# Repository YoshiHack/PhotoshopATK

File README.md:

## Summary

PhotoshopATK is a compact, single-handed macropad designed to make editing in Adobe Photoshop faster and more efficient. It gives you quick access to your most-used editing commands so you can focus on creating instead of hunting for keyboard shortcuts. The macropad is lightweight, easy to use, and built for speed during creative work.

---
## Description 

PhotoshopATK streamlines Photoshop workflows by putting essential actions—such as undo, redo, and tool shortcuts—on dedicated physical buttons. This reduces repetitive keyboard movements, speeds up editing, and makes the overall process smoother and more comfortable.

---
## Case

The case is fully 3D-printed and built to fit within the Hackpad size requirements.
It includes:

Top shell

Bottom shell

Mounting space for the XIAO RP2040

Clearance for the PCB and switches

---
## PCB

The PCB is designed to support four mechanical switches connected directly to the XIAO RP2040. It remains compact and meets the 100×100 mm rule.

---
## Firmware

The firmware is written in KMK (CircuitPython) and maps the macropad buttons to Photoshop editing shortcuts.

Example actions:

Undo – Ctrl + Z

Redo (Photoshop) – Ctrl + Shift + Z

Other tools or shortcuts as needed

Firmware file:
/Firmware/main.py

---
## BOM (Bill Of Materiels) 

Item	Quantity	Notes
Seeed Studio XIAO RP2040	1	Main MCU
Mechanical Switches	4	Any MX-style switch
Custom PCB	1	Designed in KiCad
3D Printed Case	1 set	Top + Bottom
Keycaps	4	Any compatible keycaps
Wires/Solder	—	For assembly

---
## 📁 Repository Structure

/CAD
    PhotoshopATK.step

/PCB
    PhotoshopATK.kicad_pcb
    PhotoshopATK.kicad_sch
    PhotoshopATK.kicad_pro

/Firmware
    main.py

README.md

---
## Instructions 

Flash the KMK firmware to your XIAO RP2040

Place main.py inside the KMK folder

Connect the macropad to your computer

Open Photoshop and enjoy the faster workflow

Open-source project — feel free to build on it!

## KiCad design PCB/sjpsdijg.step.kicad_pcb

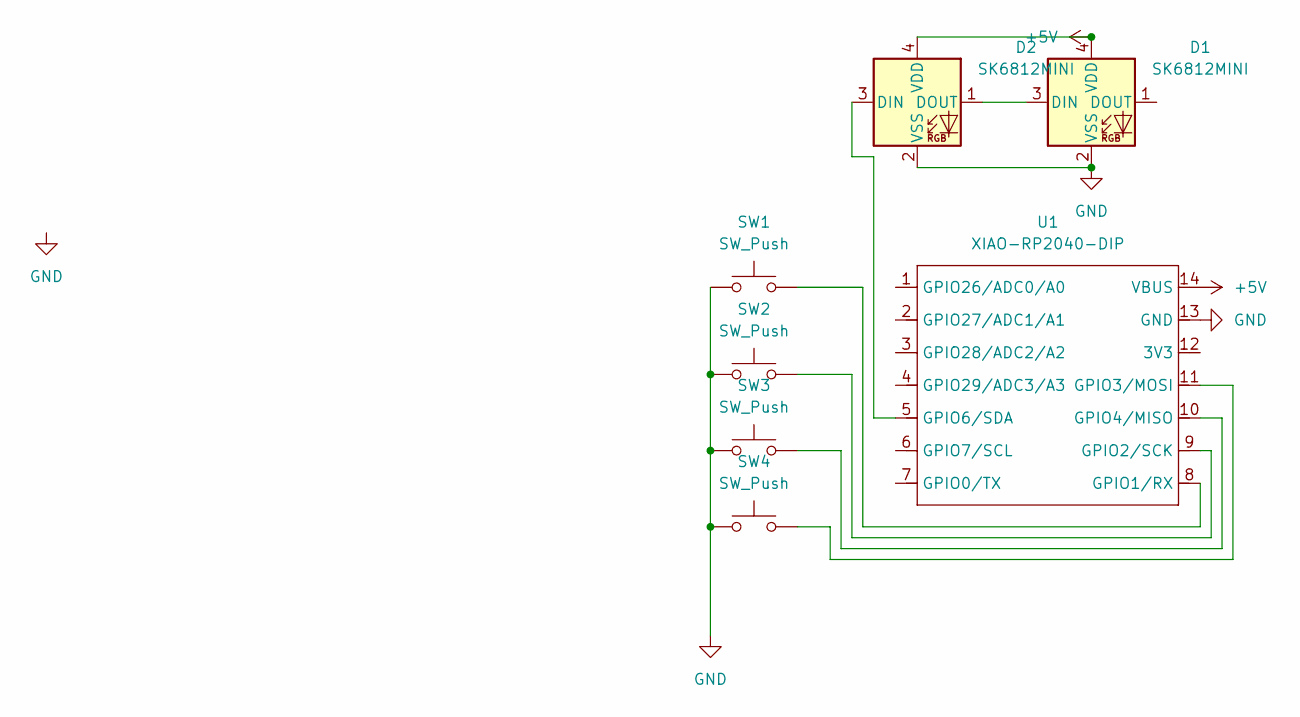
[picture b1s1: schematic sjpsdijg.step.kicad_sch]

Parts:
D1, D2: SK6812MINI; LED_SK6812MINI_PLCC4_3.5x3.5mm_P1.75mm
SW1, SW2, SW3, SW4: SW_Push; SW_Cherry_MX_1.00u_PCB
U1: XIAO-RP2040-DIP; XIAO-RP2040-SMD

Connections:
+5V: D1.4 (VDD), D2.4 (VDD), U1.14 (VBUS)
GND: D1.2 (VSS), D2.2 (VSS), SW1.1, SW2.1, SW3.1, SW4.1, U1.13 (GND)
unnamed: D1.3 (DIN), D2.1 (DOUT)
unnamed: D2.3 (DIN), U1.5 (GPIO6/SDA)
unnamed: SW1.2, U1.8 (GPIO1/RX)
unnamed: SW2.2, U1.9 (GPIO2/SCK)
unnamed: SW4.2, U1.11 (GPIO3/MOSI)
unnamed: SW3.2, U1.10 (GPIO4/MISO)

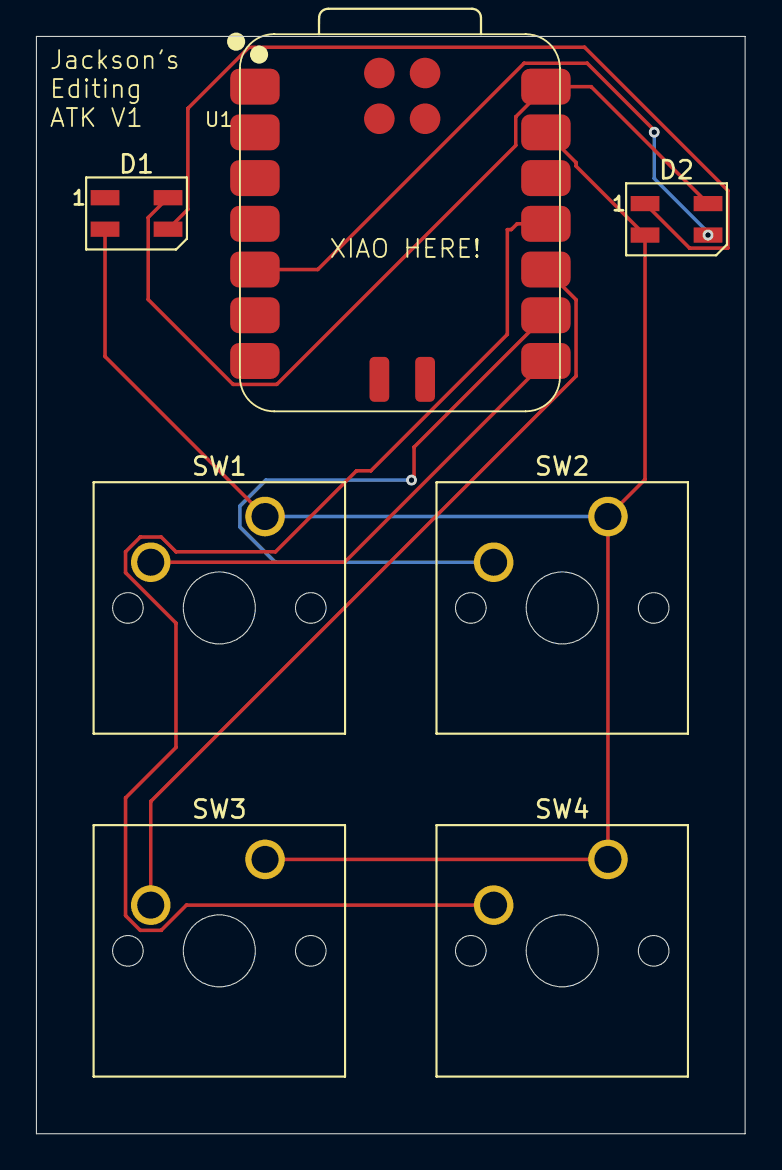
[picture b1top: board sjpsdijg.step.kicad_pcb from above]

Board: 2 copper layers, 39.4 x 61.0 mm, 7 parts (0 on the bottom side), 8 nets.

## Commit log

2025-12-04 Add Photoshop Support
2025-12-04 Add initial README for Firmware directory
2025-12-04 Add readme for CAD model repository
2025-12-04 Add README file for .STEP file description
2025-12-04 Add initial readme for PCB project
2025-12-04 Rename sjpsdijg.step.kicad_pro to PhotoshopATk.step.kicad_pro
2025-12-04 Rename sjpsdijg.step.kicad_sch to PhotoshopATK.step.kicad_sch
2025-12-04 Rename Jackson's ATK.step to PhotoshopATK.step
2025-12-04 Create dfsdf
2025-12-04 Update README formatting and image placeholder
2025-12-04 Refactor README for improved formatting
    Updated README formatting and removed placeholder image.
2025-12-04 Fix header formatting in README.md
2025-12-17 Revise README.md for improved clarity and detail
    Updated README.md to enhance clarity and engagement, including sections on purpose, case design, PCB overview, firmware, and usage instructions.
2025-12-17 Revise README for improved clarity and detail
    Updated the README to enhance clarity and detail about the PhotoshopATK macropad, including its purpose, case design, PCB overview, firmware, and bill of materials.
2025-12-17 Revise README.md for improved organization and detail
    Updated README.md to enhance structure and clarity, including sections for Summary, Description, Case, PCB, BOM, Repository Structure, and Instructions.
2025-12-17 Add BOM.csv for project components listing
2025-12-17 Update Summary heading level in README.md
    Changed heading level from H3 to H2 for summary section.
